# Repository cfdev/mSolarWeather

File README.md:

# mSolarWeather
This project use the SparkFun weather meter kit and other sensors,
the brain of this Weather Station is an ESP32-S3-WROOM-1.

## Alimentation
- Battery 32700 LiFePo4 7200mAh
- SolarPanel 5 Volts 400mA

## Sensors
1. Internal Temperature (BME280)
2. Humidity (BME280)
3. Barometric Pressure (BME280)
4. External Temperature (PT100)
5. Wind Speed ( Sparkfun Weather Meter )
6. Wind Direction ( Sparkfun Weather Meter )
7. Rain Gauge ( Sparkfun Weather Meter )

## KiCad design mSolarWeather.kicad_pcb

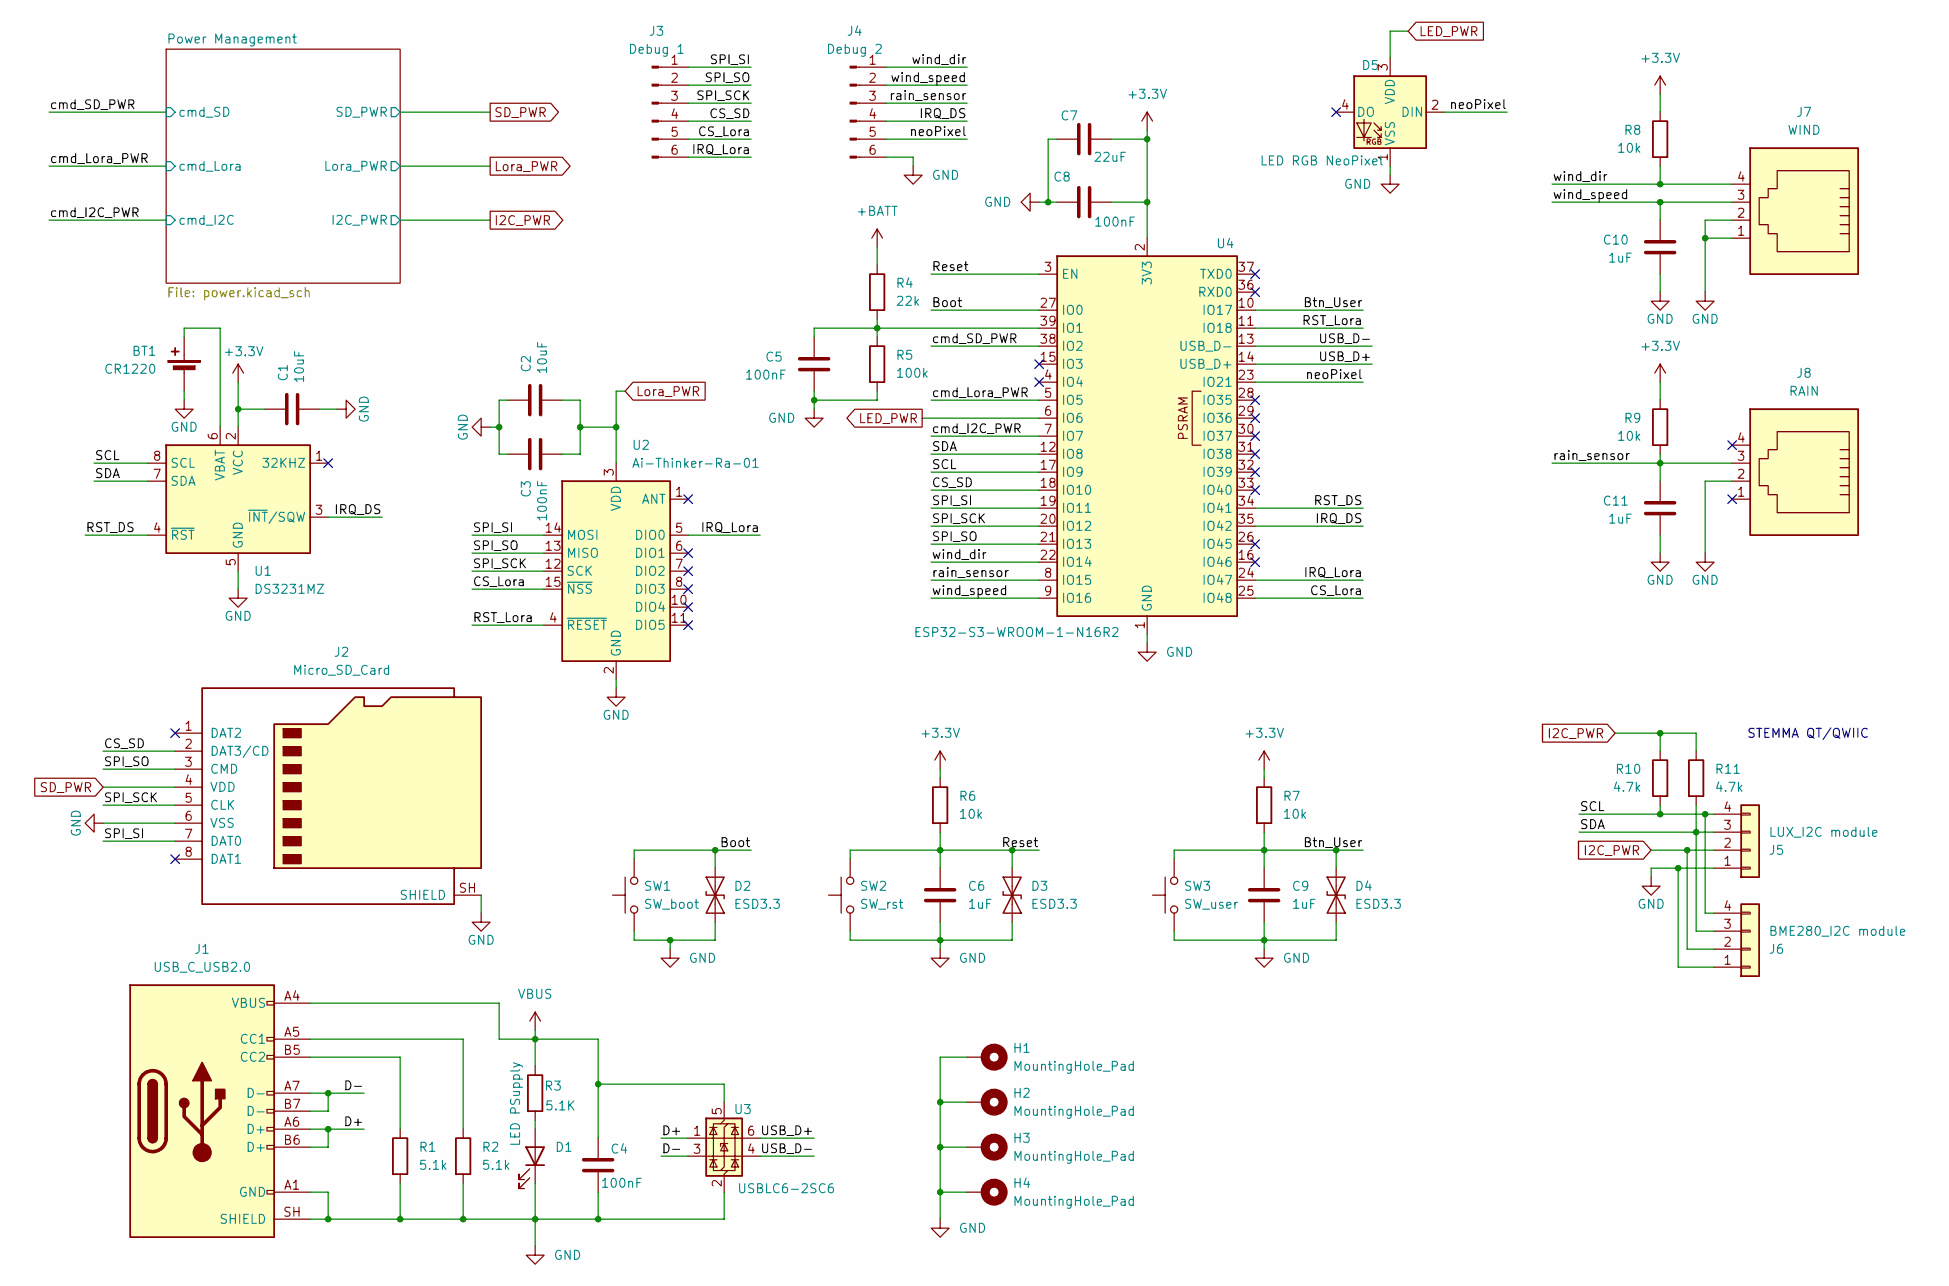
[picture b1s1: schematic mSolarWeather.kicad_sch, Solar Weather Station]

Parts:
BT1: CR1220; BatteryHolder_Keystone_500
C1, C2: 10uF; C_1206_3216Metric_Pad1.33x1.80mm_HandSolder
C3, C4, C5, C8: 100nF; C_0805_2012Metric_Pad1.18x1.45mm_HandSolder
C6, C9, C10, C11: 1uF; C_0805_2012Metric_Pad1.18x1.45mm_HandSolder
C7: 22uF; C_1210_3225Metric_Pad1.33x2.70mm_HandSolder
D1: LED PSupply; LED_PLCC-2_3.4x3.0mm_KA
D2, D3, D4: ESD3.3; D_SOD-923
D5: LED RGB NeoPixel; LED_Inolux_IN-PI554FCH_PLCC4_5.0x5.0mm_P3.2mm
H1, H2, H3, H4: MountingHole_Pad; MountingHole_3.2mm_M3_Pad_Via
J1: USB_C_USB2.0; USB_C_Receptacle_Palconn_UTC16-G
J2: Micro_SD_Card; microSD_HC_Hirose_DM3AT-SF-PEJM5
J3: Debug 1; PinHeader_1x06_P2.54mm_Vertical
J4: Debug 2; PinHeader_1x06_P2.54mm_Vertical
J5: LUX_I2C module; JST_SH_SM04B-SRSS-TB_1x04-1MP_P1.00mm_Horizontal
J6: BME280_I2C module; JST_SH_SM04B-SRSS-TB_1x04-1MP_P1.00mm_Horizontal
J7: WIND; RJ12_x04_Horizontal
J8: RAIN; RJ12_x04_Horizontal
R1, R2: 5.1k; R_0805_2012Metric_Pad1.20x1.40mm_HandSolder
R3: 5.1K; R_0805_2012Metric_Pad1.20x1.40mm_HandSolder
R4: 22k; R_0805_2012Metric_Pad1.20x1.40mm_HandSolder
R5: 100k; R_0805_2012Metric_Pad1.20x1.40mm_HandSolder
R6, R7, R8, R9: 10k; R_0805_2012Metric_Pad1.20x1.40mm_HandSolder
R10, R11: 4.7k; R_0805_2012Metric_Pad1.20x1.40mm_HandSolder
SW1: SW_boot; SW_Push_1P1T_NO_CK_KSC9xxG
SW2: SW_rst; SW_Push_1P1T_NO_CK_KSC9xxG
SW3: SW_user; SW_Push_1P1T_NO_CK_KSC9xxG
U1: DS3231MZ; SOIC-8_3.9x4.9mm_P1.27mm
U2: Ai-Thinker-Ra-01; Ai-Thinker-Ra-01-LoRa
U3: USBLC6-2SC6; SOT-23-6
U4: ESP32-S3-WROOM-1-N16R2; ESP32-S3-WROOM-1

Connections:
+3.3V: C1.1, C7.2, C8.2, R6.1, R7.1, R8.1, R9.1, U1.2 (VCC), U4.2 (3V3); also elsewhere on the board
+BATT: R4.1; also elsewhere on the board
/Boot: D2.2 (A2), SW1.2, U4.27 (IO0)
/Btn_User: C9.1, D4.2 (A2), R7.2, SW3.2, U4.10 (IO17)
/CS_Lora: J3.5, U2.15 (~NSS), U4.25 (IO48)
/CS_SD: J2.2 (DAT3/CD), J3.4, U4.18 (IO10)
/D+: J1.A6 (D+), J1.B6 (D+), U3.1 (I/O1)
/D-: J1.A7 (D-), J1.B7 (D-), U3.3 (I/O2)
/IRQ_DS: J4.4, U1.3 (~INT/SQW), U4.35 (IO42)
/IRQ_Lora: J3.6, U2.5 (DIO0), U4.24 (IO47)
/RST_DS: U1.4 (~RST), U4.34 (IO41)
/RST_Lora: U2.4 (~RESET), U4.11 (IO18)
/Reset: C6.1, D3.2 (A2), R6.2, SW2.2, U4.3 (EN)
/SCL: J5.4, J6.4, R10.2, U1.8 (SCL), U4.17 (IO9)
/SDA: J5.3, J6.3, R11.2, U1.7 (SDA), U4.12 (IO8)
/SPI_SCK: J2.5 (CLK), J3.3, U2.12 (SCK), U4.20 (IO12)
/SPI_SI: J2.7 (DAT0), J3.1, U2.14 (MOSI), U4.19 (IO11)
/SPI_SO: J2.3 (CMD), J3.2, U2.13 (MISO), U4.21 (IO13)
/USB_D+: U3.6 (I/O1), U4.14 (USB_D+)
/USB_D-: U3.4 (I/O2), U4.13 (USB_D-)
/cmd_I2C_PWR: U4.7 (IO7); also elsewhere on the board
/cmd_Lora_PWR: U4.5 (IO5); also elsewhere on the board
/cmd_SD_PWR: U4.38 (IO2); also elsewhere on the board
/neoPixel: D5.2 (DIN), J4.5, U4.23 (IO21)
/rain_sensor: C11.2, J4.3, J8.3, R9.2, U4.8 (IO15)
/wind_dir: J4.1, J7.4, R8.2, U4.22 (IO14)
/wind_speed: C10.2, J4.2, J7.3, U4.9 (IO16)
GND: BT1.2 (-), C1.2, C2.1, C3.1, C4.1, C5.1, C6.2, C7.1, C8.1, C9.2, C10.1, C11.1, D1.1 (K), D2.1 (A1), D3.1 (A1), D4.1 (A1), D5.1 (VSS), H1.1 (1_1), H2.1 (1_1), H3.1 (1_1), H4.1 (1_1), J1.A1 (GND), J1.A12 (GND), J1.B1 (GND), J1.B12 (GND), J1.SH (SHIELD), J2.6 (VSS), J2.SH (SHIELD), J4.6, J5.1, J6.1, J7.1, J7.2, J8.2, R1.2, R2.2, R5.2, SW1.1, SW2.1, SW3.1, U1.5 (GND), U2.2 (GND), U2.9 (GND), U2.16 (GND), U3.2 (GND), U4.1 (GND), U4.40 (GND), U4.41 (GND); also elsewhere on the board
I2C_PWR: J5.2, J6.2, R10.1, R11.1; also elsewhere on the board
LED_PWR: D5.3 (VDD), U4.6 (IO6)
Lora_PWR: C2.2, C3.2, U2.3 (VDD); also elsewhere on the board
unnamed: BT1.1 (+), U1.6 (VBAT)
unnamed: D1.2 (A), R3.2
unnamed: J1.A5 (CC1), R2.1
unnamed: J1.B5 (CC2), R1.1
unnamed: C5.2, R4.2, R5.1, U4.39 (IO1)
SD_PWR: J2.4 (VDD); also elsewhere on the board
VBUS: C4.2, J1.A4 (VBUS), J1.A9 (VBUS), J1.B4 (VBUS), J1.B9 (VBUS), R3.1, U3.5 (VBUS); also elsewhere on the board

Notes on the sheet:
STEMMA QT/QWIIC

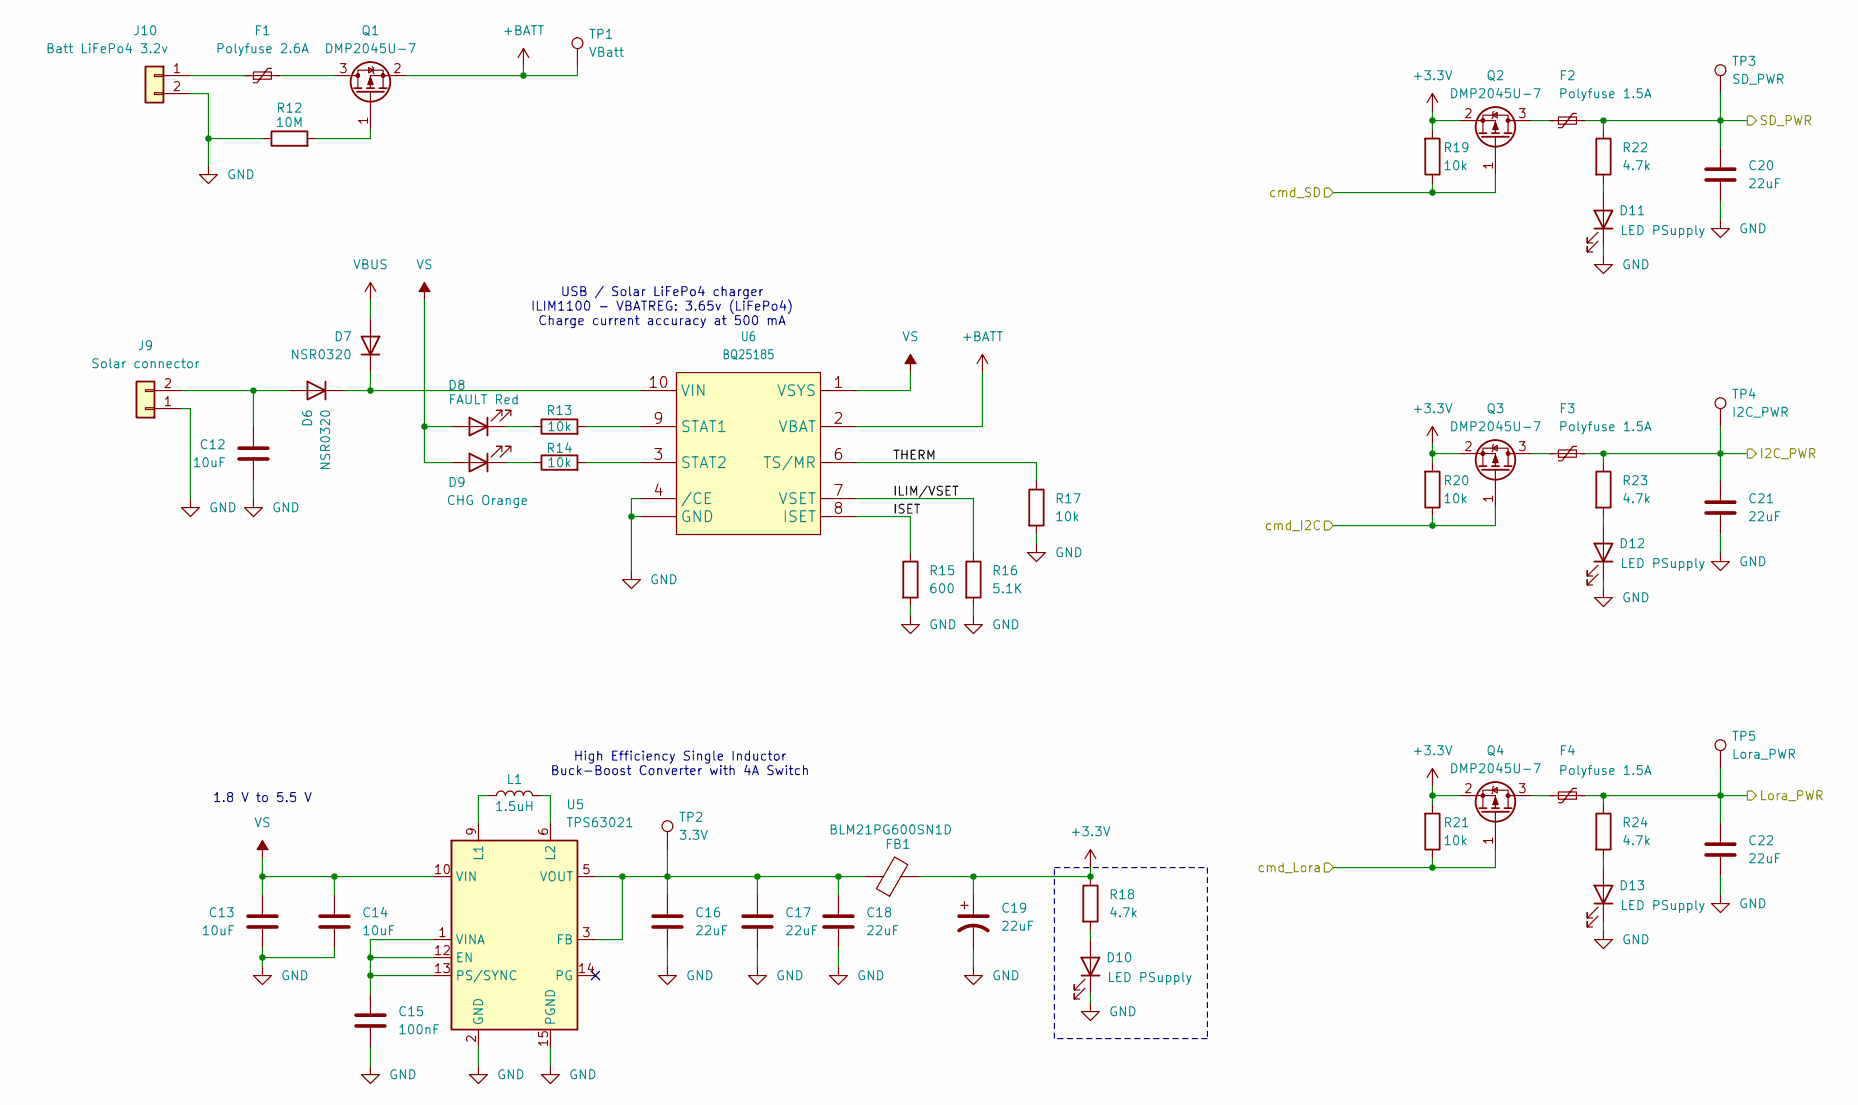
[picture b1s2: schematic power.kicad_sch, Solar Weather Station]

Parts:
C12, C13, C14: 10uF; C_1206_3216Metric_Pad1.33x1.80mm_HandSolder
C15: 100nF; C_0805_2012Metric_Pad1.18x1.45mm_HandSolder
C16, C17, C18, C20, C21, C22: 22uF; C_1210_3225Metric_Pad1.33x2.70mm_HandSolder
C19: 22uF; C_Elec_5x5.4
D6, D7: NSR0320; D_SOD-323_HandSoldering
D8: FAULT Red; LED_PLCC-2_3.4x3.0mm_KA
D9: CHG Orange; LED_PLCC-2_3.4x3.0mm_KA
D10, D11, D12, D13: LED PSupply; LED_PLCC-2_3.4x3.0mm_KA
F1: Polyfuse 2.6A; Fuse_1206_3216Metric_Pad1.42x1.75mm_HandSolder
F2, F3, F4: Polyfuse 1.5A; Fuse_1206_3216Metric_Pad1.42x1.75mm_HandSolder
FB1: BLM21PG600SN1D; L_0805_2012Metric_Pad1.05x1.20mm_HandSolder
J9: Solar connector; TerminalBlock_Phoenix_MKDS-1,5-2-5.08_1x02_P5.08mm_Horizont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
J10: Batt LiFePo4 3.2v; TerminalBlock_Phoenix_MKDS-1,5-2-5.08_1x02_P5.08mm_Horizont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
L1: 1.5uH; L_Wurth_WE-LQSH-4020; Mouser VLS3015CX-1R5M-H
Q1, Q2, Q3, Q4: DMP2045U-7; SOT-23
R12: 10M; R_0805_2012Metric_Pad1.20x1.40mm_HandSolder
R13, R14, R17, R19, R20, R21: 10k; R_0805_2012Metric_Pad1.20x1.40mm_HandSolder
R15: 600; R_0805_2012Metric_Pad1.20x1.40mm_HandSolder
R16: 5.1K; R_0805_2012Metric_Pad1.20x1.40mm_HandSolder
R18, R22, R23, R24: 4.7k; R_0805_2012Metric_Pad1.20x1.40mm_HandSolder
TP1: VBatt; TestPoint_Pad_D2.0mm
TP2: 3.3V; TestPoint_Pad_D2.0mm
TP3: SD_PWR; TestPoint_Pad_D2.0mm
TP4: I2C_PWR; TestPoint_Pad_D2.0mm
TP5: Lora_PWR; TestPoint_Pad_D2.0mm
U5: TPS63021; VSON_DSJ-14-3x4mm_P0.5mm_ThermalVias
U6: BQ25185; WSON-10-1EP_2.5x2.5mm_P0.5mm_EP1.2x2mm_ThermalVias

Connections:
+3.3V: C19.1, FB1.2, Q2.2 (S), Q3.2 (S), Q4.2 (S), R18.1, R19.2, R20.2, R21.2; also elsewhere on the board
+BATT: Q1.2 (S), TP1.1 (1_1), U6.2 (VBAT); also elsewhere on the board
/Power Management/ILIM/VSET: R16.1, U6.7 (VSET)
/Power Management/ISET: R15.1, U6.8 (ISET)
/Power Management/THERM: R17.1, U6.6 (TS/MR)
/cmd_I2C_PWR: Q3.1 (G), R20.1; also elsewhere on the board
/cmd_Lora_PWR: Q4.1 (G), R21.1; also elsewhere on the board
/cmd_SD_PWR: Q2.1 (G), R19.1; also elsewhere on the board
GND: C12.2, C13.2, C14.2, C15.2, C16.2, C17.2, C18.2, C19.2, C20.2, C21.2, C22.2, D10.1 (K), D11.1 (K), D12.1 (K), D13.1 (K), J9.1, J10.2, R12.1, R15.2, R16.2, R17.2, U5.2 (GND), U5.15 (PGND), U6.4 (/CE), U6.5 (GND), U6.11 (Thermal), U6.PAD (GND); also elsewhere on the board
I2C_PWR: C21.1, F3.2, R23.1, TP4.1 (1_1); also elsewhere on the board
Lora_PWR: C22.1, F4.2, R24.1, TP5.1 (1_1); also elsewhere on the board
unnamed: C12.1, D6.2 (A), J9.2
unnamed: D6.1 (K), D7.1 (K), U6.10 (VIN)
unnamed: D8.1 (K), R13.1
unnamed: D9.1 (K), R14.1
unnamed: D10.2 (A), R18.2
unnamed: D11.2 (A), R22.2
unnamed: D12.2 (A), R23.2
unnamed: D13.2 (A), R24.2
unnamed: F1.1, J10.1
unnamed: L1.1, U5.8 (L1), U5.9 (L1)
unnamed: L1.2, U5.6 (L2), U5.7 (L2)
unnamed: F1.2, Q1.3 (D)
unnamed: Q1.1 (G), R12.2
unnamed: F2.1, Q2.3 (D)
unnamed: F3.1, Q3.3 (D)
unnamed: F4.1, Q4.3 (D)
unnamed: C15.1, U5.1 (VINA), U5.12 (EN), U5.13 (PS/SYNC)
unnamed: C16.1, C17.1, C18.1, FB1.1, TP2.1 (1_1), U5.3 (FB), U5.4 (VOUT), U5.5 (VOUT)
unnamed: R13.2, U6.9 (STAT1)
unnamed: R14.2, U6.3 (STAT2)
SD_PWR: C20.1, F2.2, R22.1, TP3.1 (1_1); also elsewhere on the board
VBUS: D7.2 (A); also elsewhere on the board
VS: C13.1, C14.1, D8.2 (A), D9.2 (A), U5.10 (VIN), U5.11 (VIN), U6.1 (VSYS)

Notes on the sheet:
High Efficiency Single Inductor Buck-Boost Converter with 4A Switch
USB / Solar LiFePo4 charger ILIM1100 - VBATREG: 3.65v (LiFePo4) Charge current accuracy at 500 mA
1.8 V to 5.5 V

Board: 2 copper layers, 105 parts (0 on the bottom side), 62 nets, no tracks yet.

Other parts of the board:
kibuzzard-6AF322C1: G***; kibuzzard-6AF322C1
kibuzzard-6AF322C8: G***; kibuzzard-6AF322C8
kibuzzard-6AF323A8: G***; kibuzzard-6AF323A8
kibuzzard-6AF323B4: G***; kibuzzard-6AF323B4
kibuzzard-6AF32232: G***; kibuzzard-6AF32232
kibuzzard-6AF32254: G***; kibuzzard-6AF32254
kibuzzard-6AF32296: G***; kibuzzard-6AF32296

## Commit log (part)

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2025-07-05 update kicad 9
2025-07-05 Add Stemma QT connector
    JST_SH_SM04B like ?
2025-07-20 Create TPS63021 symbol
    Use the pin stacking technique for hidden pins
2025-07-20 Beginning to create TPS63021 footprint
    ref to the datasheet page DSJ (R-PVSON-N14)
2025-07-20 Create fp-lib-table
2025-07-20 Create sym-lib-table
2025-07-20 Update schematic with the TPS63021
2026-05-28 update schematic
    add SD card
    add RTC chip
    add Lora module
    update BQ25185 configuration for LiFePo4
